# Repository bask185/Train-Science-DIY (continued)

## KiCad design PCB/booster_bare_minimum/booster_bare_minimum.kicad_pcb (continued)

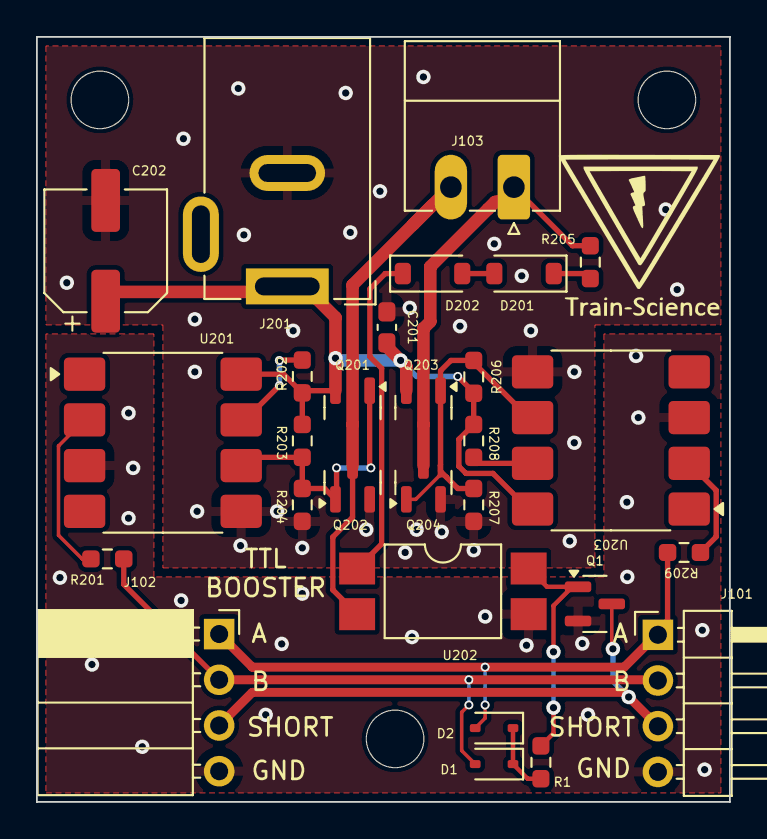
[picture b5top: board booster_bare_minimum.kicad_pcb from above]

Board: 2 copper layers, 38.5 x 42.5 mm, 28 parts (0 on the bottom side), 19 nets.

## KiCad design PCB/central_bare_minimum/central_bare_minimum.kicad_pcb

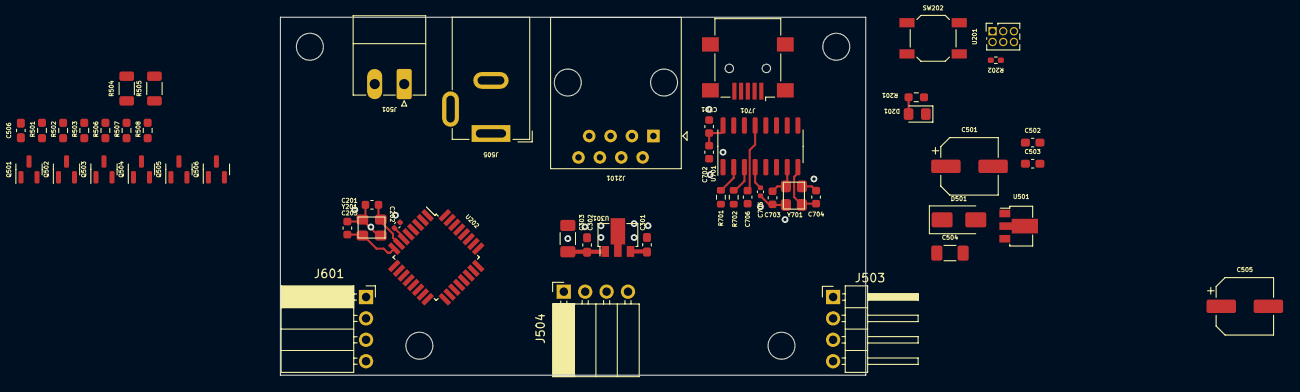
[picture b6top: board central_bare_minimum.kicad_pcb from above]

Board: 2 copper layers, 69.5 x 42.5 mm, 53 parts (0 on the bottom side), 41 nets.

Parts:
C201, C203: 12pF; C_0603_1608Metric
C202, C705: 100nF; C_0402_1005Metric
C301, C502: 330nF; C_0603_1608Metric_Pad1.08x0.95mm_HandSolder
C302, C503, C506: 100nF; C_0603_1608Metric_Pad1.08x0.95mm_HandSolder
C303, C504: 100uF; C_1206_3216Metric_Pad1.33x1.80mm_HandSolder
C501, C505: 100uF; CP_Elec_6.3x5.9
C701: 10uF; C_0603_1608Metric
C702, C706: 100nF; C_0603_1608Metric
C703, C704: 22pF; C_0603_1608Metric
D201: LED; LED_0805_2012Metric_Pad1.15x1.40mm_HandSolder
D501: SS53; D_SMA
J501: track; PhoenixContact_MC_1,5_2-G-3.5_1x02_P3.50mm_Horizontal
J503: Conn_01x04_Pin; PinHeader_1x04_P2.54mm_Horizontal
J504, J601: Conn_01x04_Socket; PinSocket_1x04_P2.54mm_Horizontal
J505: Barrel_Jack; BarrelJack_GCT_DCJ200-10-A_Horizontal
J701: USB_B_Mini; USB_Mini-B_Lumberg_2486_01_Horizontal
J2101: RJ45; RJ45_Amphenol_54602-x08_Horizontal
Q501, Q506: NPN_TOR; SOT-23
Q502, Q504: P-channel; SOT-23
Q503, Q505: N-channel; SOT-23
R201: 6k2; R_0603_1608Metric_Pad0.98x0.95mm_HandSolder
R202: 10k; R_0402_1005Metric_Pad0.72x0.64mm_HandSolder
R501, R508: 1k5; R_0603_smalltext
R502, R506: 10k; R_0603_smalltext
R503, R507: 15k; R_0603_smalltext
R504, R505: 0R1; R_1206_3216Metric
R701, R702: 1k; R_0603_1608Metric
SW202: default_switch
U201: HEADER_3x2; PinSocket_2x03_P1.27mm_Vertical
U202: ATmega328-A; TQFP-32_7x7mm_P0.8mm
U301: L78L05_SOT89; SOT-89-3
U501: L78L12_SOT89; SOT-89-3
U701: CH340G; SOIC-16_3.9x9.9mm_P1.27mm
Y201: Crystal_GND2; crystal_arduino
Y701: Crystal; crystal_arduino

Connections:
+5V: C202.1, C302.1, C303.1, C701.1, C702.1, J504.2, J701.1 (VBUS), R201.1, R202.1, U201.5, U202.4 (VCC), U202.6 (VCC), U202.18 (AVCC), U301.1 (OUT), U701.16 (VCC)
+12V: C301.1, C503.1, C504.1, J2101.1, U301.3 (IN), U501.1 (OUT)
/CPU/LED: D201.1 (K), U201.4, U202.17 (PB5)
/CPU/MISO: U201.6, U202.16 (PB4)
/CPU/MOSI: U201.3, U202.15 (PB3)
/CPU/RESET: C706.2, R202.2, SW202.2 (B), U201.2, U202.29 (~RESET/PC6)
/CPU/Rx: R701.2, U202.30 (PD0)
/CPU/SCL: J504.4, U202.28 (PC5)
/CPU/SDA: J504.3, U202.27 (PC4)
/CPU/Tx: R702.1, U202.31 (PD1)
/CPU/X1: C201.2, U202.7 (XTAL1/PB6), Y201.1
/CPU/X2: C203.2, U202.8 (XTAL2/PB7), Y201.3
/CPU/booster1.A: J601.1, U202.10 (PD6)
/CPU/booster1.B: J601.2, U202.11 (PD7)
/CPU/booster2.A: J503.1, U202.23 (PC0)
/CPU/booster2.B: J503.2, U202.24 (PC1)
/CPU/clock: J2101.4, U202.1 (PD3)
/CPU/data: J2101.2, U202.32 (PD2)
/CPU/load: J2101.6, U202.2 (PD4)
/CPU/prog.A: R501.2, U202.12 (PB0)
/CPU/prog.B: R508.2, U202.13 (PB1)
/CPU/s88reset: J2101.7, U202.9 (PD5)
/Hbridge/ShortCircuit: Q501.2 (E), Q503.2 (S), Q505.2 (S), Q506.2 (E), R503.2, R504.1, R505.1, R507.2
/Hbridge/Track_A: J501.1, Q502.3 (D), Q503.3 (D)
/Hbridge/Track_B: J501.2, Q504.3 (D), Q505.3 (D)
GND: C201.1, C202.2, C203.1, C301.2, C302.2, C303.2, C501.2, C502.2, C503.2, C504.2, C505.2, C506.1, C701.2, C702.2, C703.2, C704.2, C705.1, J503.4, J504.1, J505.2, J601.4, J701.5 (GND), J701.6 (Shield), J2101.3, J2101.5, R504.2, R505.2, SW202.1 (A), U201.1, U202.3 (GND), U202.5 (GND), U202.21 (GND), U301.2 (GND), U501.2 (GND), U701.1 (GND), Y201.2 (GND), Y201.4 (GND), Y701.2 (GND), Y701.4 (GND)
unnamed: D201.2 (A), R201.2
unnamed: C501.1, C502.1, D501.1 (K), U501.3 (IN)
unnamed: J701.3 (D+), U701.5 (UD+)
unnamed: J701.2 (D-), U701.6 (UD-)
unnamed: Q501.1 (B), R501.1
unnamed: Q501.3 (C), Q502.1 (G), Q503.1 (G), R502.2, R503.1
unnamed: Q504.1 (G), Q505.1 (G), Q506.3 (C), R506.2, R507.1
unnamed: Q506.1 (B), R508.1
unnamed: R702.2, U701.3 (RXD)
unnamed: R701.1, U701.2 (TXD)
unnamed: C705.2, U701.4 (V3)
unnamed: C703.1, U701.7 (XI), Y701.1
unnamed: C704.1, U701.8 (XO), Y701.3
unnamed: C706.1, U701.13 (~DTR)
VCC: C505.1, C506.2, D501.2 (A), J505.1, Q502.2 (S), Q504.2 (S), R502.1, R506.1
